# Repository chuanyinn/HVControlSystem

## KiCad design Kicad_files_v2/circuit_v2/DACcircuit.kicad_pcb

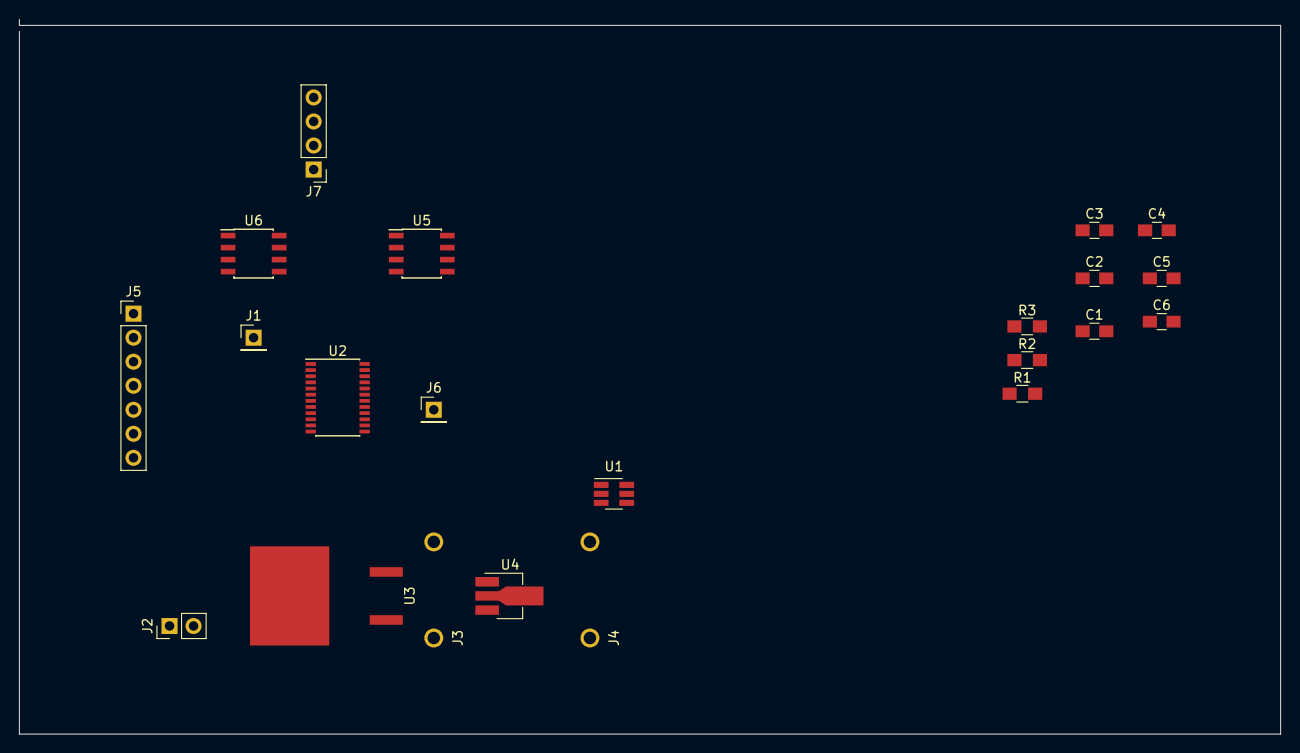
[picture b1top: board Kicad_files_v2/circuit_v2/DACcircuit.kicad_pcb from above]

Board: 4 copper layers, 133.4 x 75.6 mm, 22 parts (0 on the bottom side), 23 nets, no tracks yet.

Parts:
C1, C3, C5, C6: 0.1uF; C_0805_HandSoldering
C2, C4: 10uF; C_0805_HandSoldering
J1, J6: Conn_01x01; Pin_Header_Straight_1x01_Pitch2.54mm
J2: Conn_01x02; Pin_Header_Straight_1x02_Pitch2.54mm
J3, J4: Conn_01x01; BANANA
J5: Conn_01x07; Pin_Header_Straight_1x07_Pitch2.54mm
J7: Conn_01x04; Pin_Header_Straight_1x04_Pitch2.54mm
R1, R2, R3: 10k; R_0805_HandSoldering
U1: SN74LVC1G3157; SOT-23-6_Handsoldering
U2: AD5724R; TSSOP-24_4.4x7.8mm_Pitch0.65mm
U3: NCV8674
U4: MCP1754; SOT-89-3_Handsoldering
U5, U6: LTC2058; SOIC-8_3.9x4.9mm_Pitch1.27mm

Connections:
/3V3: C1.1, C2.1, R1.1, R2.2, R3.2, U1.4, U2.14
/3V3PS: U1.1, U1.5, U4.3
/3V3Pi: J2.2, U1.3
/+12V: C3.1, C4.1, C5.1, C6.1, U2.24, U3.3, U5.8, U6.8
/+15V: J3.1, U3.1, U4.1
/CLR: J5.5, R1.2, U2.11
/LDAC: J5.4, R3.1, U2.10
/MISO: J5.6, U2.16
/MOSI: J5.3, U2.9
/MUX: J5.7, U1.6
/OUT1: U2.3, U5.3
/OUT2: J1.1, U2.4, U5.5
/OUT3: U2.23, U6.3
/OUT4: U2.22, U6.5
/OUTA: J7.1, U5.1, U5.2
/OUTB: J7.2, U5.6, U5.7
/OUTC: J7.3, U6.1, U6.2
/OUTD: J7.4, U6.6, U6.7
/SCK: J5.2, U2.8
/SYNC: J5.1, R2.1, U2.7
GNDA: C3.2, C4.2, C5.2, C6.2, J4.1, U1.2, U2.1, U2.15, U2.18, U2.19, U2.20, U2.21, U3.2, U5.4, U6.4
GNDD: C1.2, C2.2, J2.1, U2.5, U4.2
unnamed: J6.1, U2.17

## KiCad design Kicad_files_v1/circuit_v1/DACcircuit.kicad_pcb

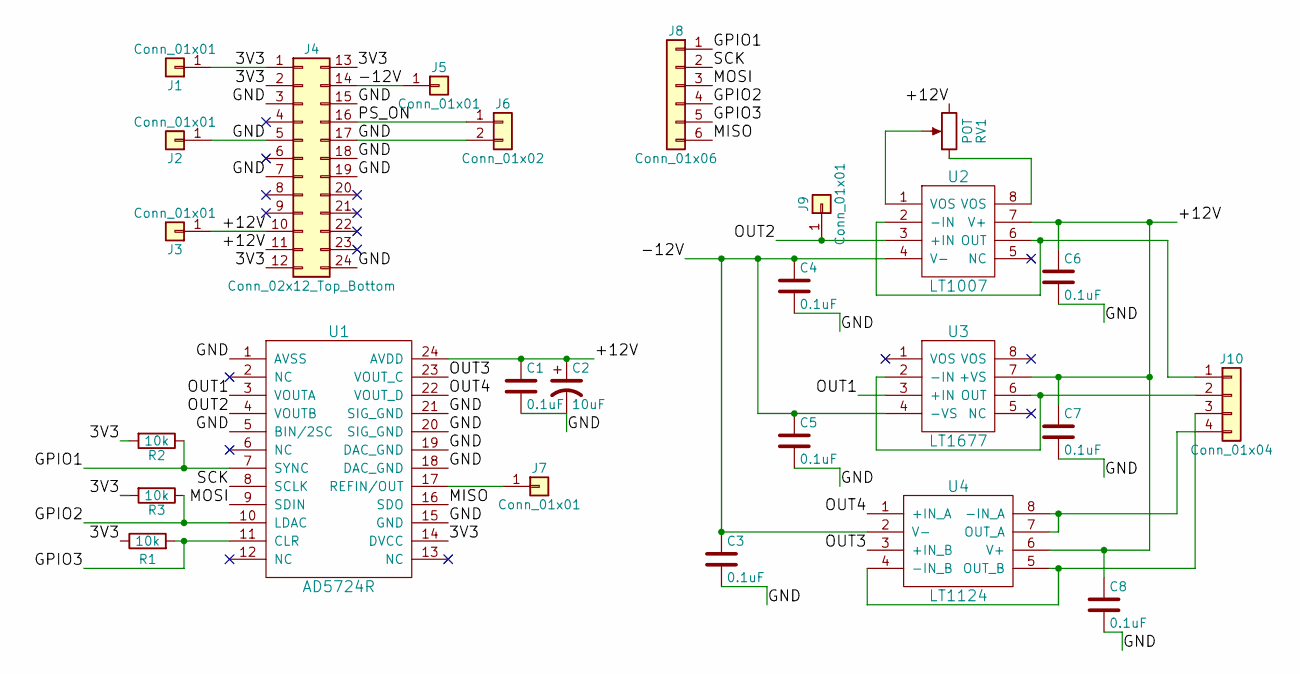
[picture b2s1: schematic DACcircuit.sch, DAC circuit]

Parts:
C1, C3, C4, C5, C6, C7, C8: 0.1uF; C_0805_HandSoldering
C2: 10uF; CP_Elec_5x5.3
J1, J2, J3, J5, J7, J9: Conn_01x01; Pin_Header_Straight_1x01_Pitch2.54mm
J4: Conn_02x12_Top_Bottom; atx_24pin
J6: Conn_01x02; Pin_Header_Straight_1x02_Pitch2.54mm
J8: Conn_01x06; Pin_Header_Straight_1x06_Pitch2.54mm
J10: Conn_01x04; Pin_Header_Straight_1x04_Pitch2.54mm
R1, R2, R3: 10k; R_0805_HandSoldering
RV1: POT; TC33X-2
U1: AD5724R; TSSOP-24_4.4x7.8mm_Pitch0.65mm
U2: LT1007; SO-8
U3: LT1677; SO-8
U4: LT1124; SO-8

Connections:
/3V3: J1.1, J4.1, J4.2, J4.12, J4.13, R1.1, R2.2, R3.2, U1.14 (DVCC)
/+12V: C1.1, C2.1, C6.1, C7.1, C8.1, J3.1, J4.10, J4.11, RV1.3, U1.24 (AVDD), U2.7 (V+), U3.7 (+VS), U4.6 (V+)
/-12V: C3.1, C4.1, C5.1, J4.14, J5.1, U2.4 (V-), U3.4 (-VS), U4.2 (V-)
/GND: C1.2, C2.2, C3.2, C4.2, C5.2, C6.2, C7.2, C8.2, J2.1, J4.3, J4.5, J4.7, J4.15, J4.17, J4.18, J4.19, J4.24, J6.2, U1.1 (AVSS), U1.5 (BIN/2SC), U1.15 (GND), U1.18 (DAC_GND), U1.19 (DAC_GND), U1.20 (SIG_GND), U1.21 (SIG_GND)
/GPIO1: J8.1, R2.1, U1.7 (SYNC)
/GPIO2: J8.4, R3.1, U1.10 (LDAC)
/GPIO3: J8.5, R1.2, U1.11 (CLR)
/MISO: J8.6, U1.16 (SDO)
/MOSI: J8.3, U1.9 (SDIN)
/OUT1: U1.3 (VOUTA), U3.3 (+IN)
/OUT2: J9.1, U1.4 (VOUTB), U2.3 (+IN)
/OUT3: U1.23 (VOUT_C), U4.3 (+IN_B)
/OUT4: U1.22 (VOUT_D), U4.1 (+IN_A)
/PS_ON: J4.16, J6.1
/SCK: J8.2, U1.8 (SCLK)
unnamed: J7.1, U1.17 (REFIN/OUT)
unnamed: J10.1, U2.2 (-IN), U2.6 (OUT)
unnamed: J10.2, U3.2 (-IN), U3.6 (OUT)
unnamed: J10.3, U4.4 (-IN_B), U4.5 (OUT_B)
unnamed: J10.4, U4.7 (OUT_A), U4.8 (-IN_A)
unnamed: RV1.1, U2.8 (VOS)
unnamed: RV1.2, U2.1 (VOS)

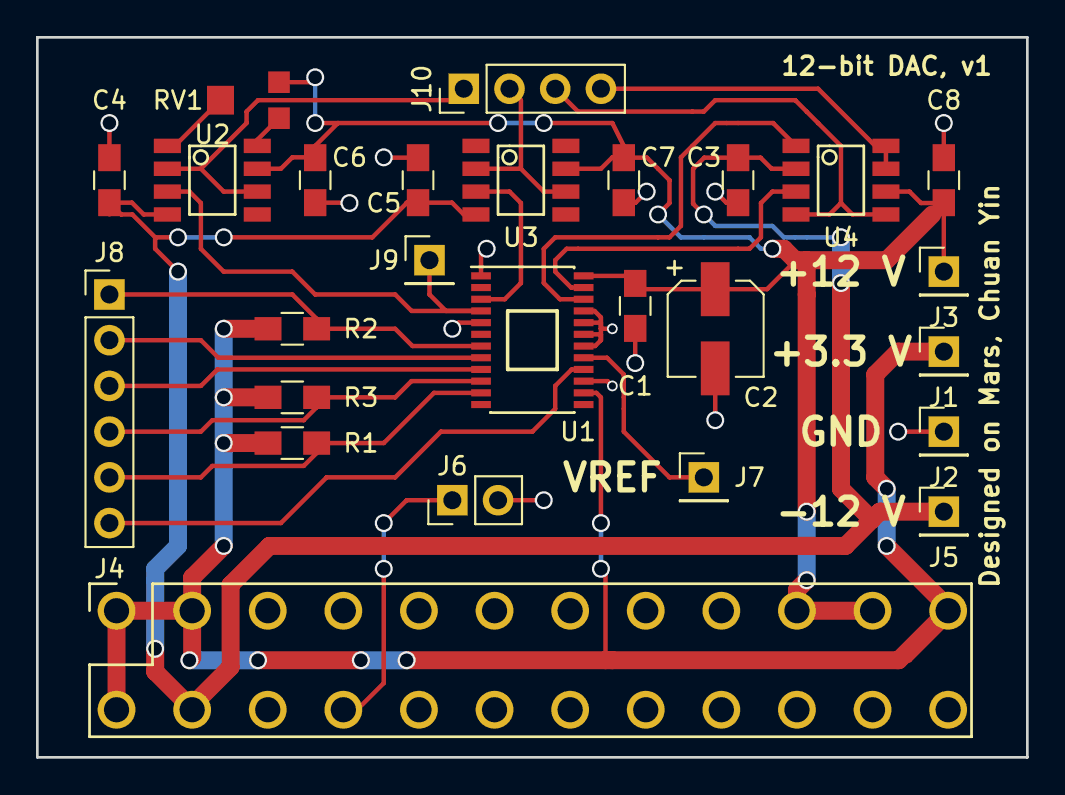
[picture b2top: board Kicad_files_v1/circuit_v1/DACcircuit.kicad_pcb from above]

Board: 2 copper layers, 55.0 x 40.0 mm, 26 parts (0 on the bottom side), 22 nets.

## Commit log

2018-11-14 Initial hardware commit
